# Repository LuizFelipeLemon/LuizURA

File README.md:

# URA
Minhas coisas que fiz no projeto

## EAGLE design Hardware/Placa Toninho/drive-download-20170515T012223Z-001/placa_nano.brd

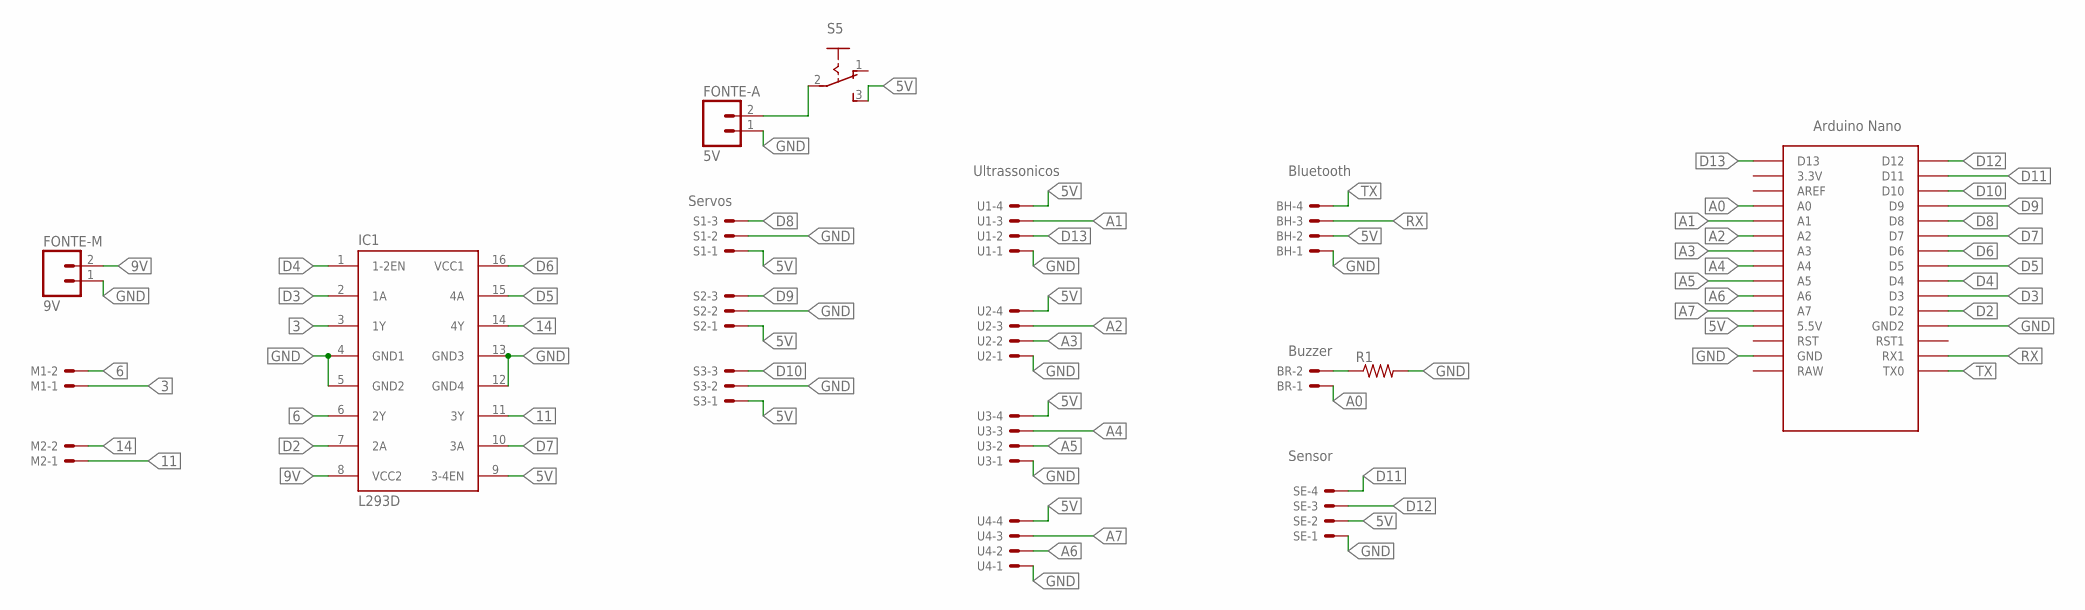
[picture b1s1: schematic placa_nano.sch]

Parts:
BH: 22-23-2041
BR: 22-23-2021
FONTE-A: 5V; 02P
FONTE-M: 9V; 02P
IC1: L293D; DIL16
M1, M2: 22-23-2021
R1: R-US_0207/10; 0207/10
S1, S2, S3: 22-23-2031
S5: 255SB
SE: 22-23-2041
U1, U2, U3, U4: 22-23-2041
U$1: NANO

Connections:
3: IC1.3 (1Y), M1.1
5V: BH.2, FONTE-A.2, IC1.9 (3-4EN), S1.1, S2.1, S3.1, S5.2, S5.3 (S), SE.2, U1.4, U2.4, U3.4, U4.4, U$1.5V (5.5V)
6: IC1.6 (2Y), M1.2
9V: FONTE-M.2, IC1.8 (VCC2)
11: IC1.11 (3Y), M2.1
14: IC1.14 (4Y), M2.2
A0: BR.1, U$1.A0
A1: U1.3, U$1.A1
A2: U2.3, U$1.A2
A3: U2.2, U$1.A3
A4: U3.3, U$1.A4
A5: U3.2, U$1.A5
A6: U4.2, U$1.A6
A7: U4.3, U$1.A7
D2: IC1.7 (2A), U$1.D2
D3: IC1.2 (1A), U$1.D3
D4: IC1.1 (1-2EN), U$1.D4
D5: IC1.15 (4A), U$1.D5
D6: IC1.16 (VCC1), U$1.D6
D7: IC1.10 (3A), U$1.D7
D8: S1.3, U$1.D8
D9: S2.3, U$1.D9
D10: S3.3, U$1.D10
D11: SE.4, U$1.D11
D12: SE.3, U$1.D12
D13: U1.2, U$1.D13
GND: BH.1, FONTE-A.1, FONTE-M.1, IC1.4 (GND1), IC1.5 (GND2), IC1.12 (GND4), IC1.13 (GND3), R1.2, S1.2, S2.2, S3.2, SE.1, U1.1, U2.1, U3.1, U4.1, U$1.GND, U$1.GND1 (GND2)
unnamed: BR.2, R1.1
RX: BH.3, U$1.RX1
TX: BH.4, U$1.TX0

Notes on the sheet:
Servos
Ultrassonicos
Bluetooth
Buzzer
Sensor

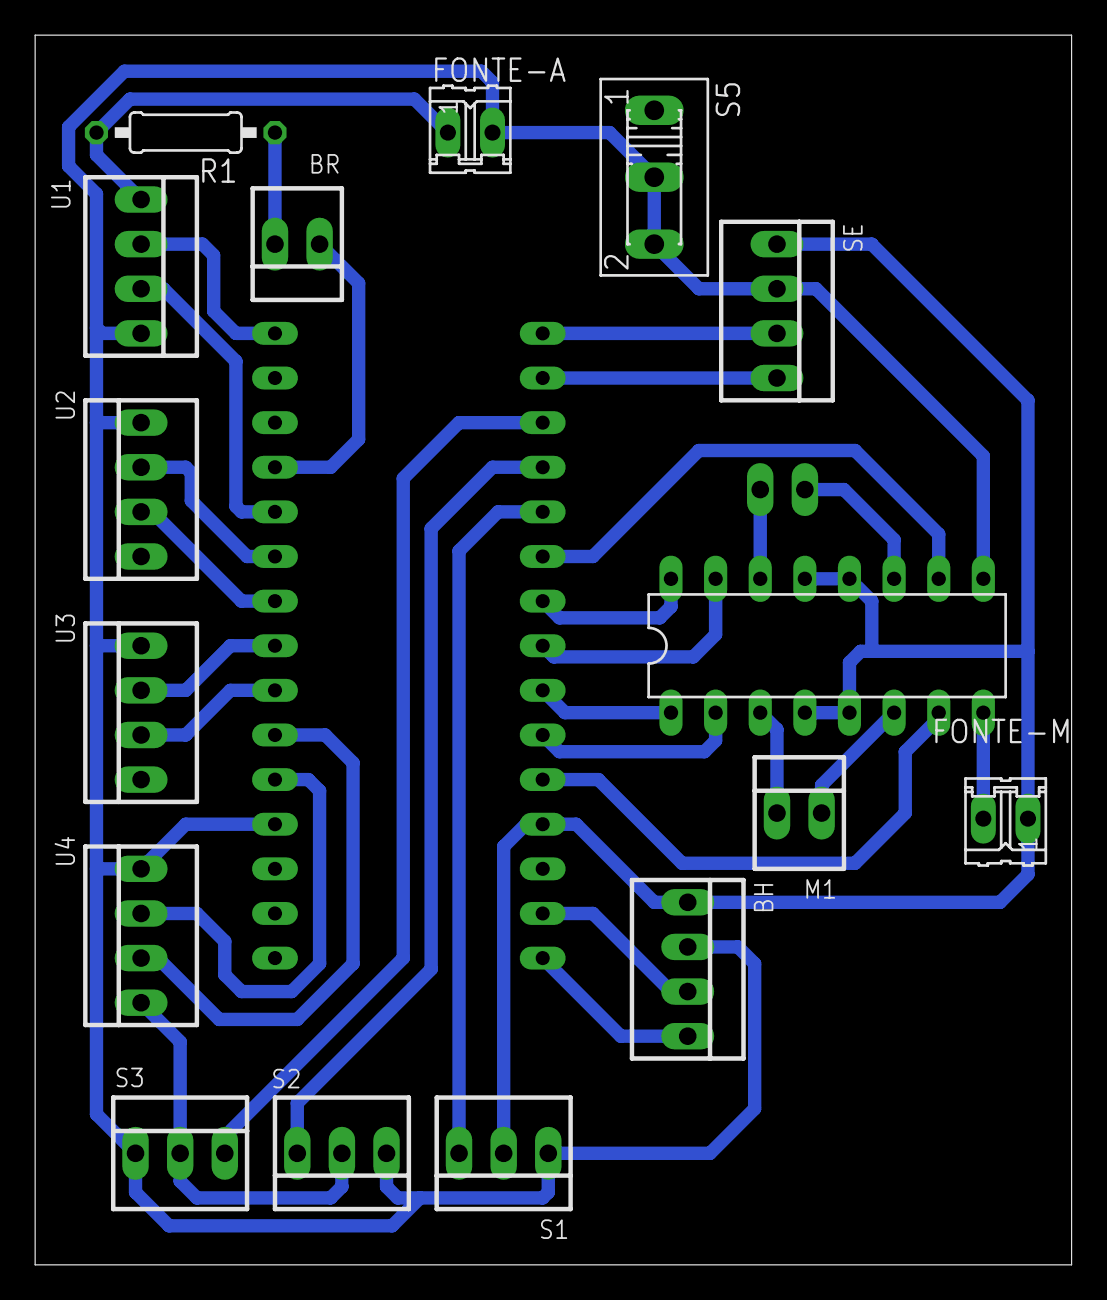
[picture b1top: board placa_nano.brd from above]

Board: 2 copper layers, 59.0 x 70.0 mm, 18 parts (1 on the bottom side), 30 nets.

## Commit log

2017-04-18 Adicionando código a ser documentado
2017-04-18 Rename Hardware/Blink.ino to Hardware/Blink/Blink.ino
2017-04-20 minha parte do código
2017-04-24 Mais comentários...
2017-04-27 Testando
2017-04-27 COMITANDO
2017-05-07 PRimeiro código feito
2017-05-07 Update luiz.cpp
    svsdvbg
2017-05-08 Update luiz.cpp
    asgf
2017-05-08 Código errado
2017-05-08 updating...
2017-05-15 Starting API
2017-05-15 Adicionando libaries
